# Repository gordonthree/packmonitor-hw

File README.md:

# Smart battery power monitor project

### A slim circuit board for managing charge and discharge of multi-cell LiFePo4 battery packs. Intended to track state of charge by coulomb counting and prevent battery pack damage from over discharge, over current and over temperature conditions.

## Goals:

1. Monitor and record total amperage in and out
2. Monitor and record temperature, ideally three places
3. Monitor and record pack voltage
4. Provide under-voltage disconnect
5. Provide over-temperature disconnect

## Features:

1. Atmel AVR Micro: ATMEGA4808 TQFP-32
1. Hall effect current sensor: TMCS1108 
   * Check my inventory for ACS7xx sensors!
1. FRAM data storage : I2C FM24C64B
1. Hot swap buffer: I2C TCA4311a, PCA9508
1. Host side i2c mux: PCA9545A
1. Max PCB width 18mm
1. Precision fixed resistor for thermistors
   * Thermistors: NRL1504F3950B1F
1.
   * MCU ADC does all measurements, for better or worse.

## Connectors:

1. Battery side
   * Battery In and Out (14 ga) - WAGO screw cage
   * 6-pin jst-xh vertical for three thermistors
1. Upstream interface: I2C
   * JST-xh 6-pin connector +5v, GND, SCL, GND, SDA, GND
   * TCA4311 on battery side
   * I2C switch on host side (might not need)

## Indicators:

* No onboard LEDs planned

## Client Commands:

* See [PackMonitor](https://github.com/gordonthree/packmonitor) for software details

## Questions:

* Will I finish in time?

## Resources:

#### ATMega4808:

* [https://www.digikey.com/en/products/detail/microchip-technology/ATMEGA4808-AUR/10444912](https://www.digikey.com/en/products/detail/microchip-technology/ATMEGA4808-AUR/10444912)
* [https://ww1.microchip.com/downloads/en/DeviceDoc/ATmega4808-09-DataSheet-DS40002173C.pdf](https://ww1.microchip.com/downloads/en/DeviceDoc/ATmega4808-09-DataSheet-DS40002173C.pdf)
* [https://github.com/MCUdude/MegaCoreX#pinout](https://github.com/MCUdude/MegaCoreX#pinout)

#### Thermistor:

* [https://www.digikey.com/en/products/detail/eaton-electronics-division/NRL1504F3950B1F/15927588](https://www.digikey.com/en/products/detail/eaton-electronics-division/NRL1504F3950B1F/15927588)
* [https://www.maximintegrated.com/en/design/technical-documents/app-notes/1/1753.html](https://www.maximintegrated.com/en/design/technical-documents/app-notes/1/1753.html)
* [https://www.jameco.com/Jameco/workshop/TechTip/temperature-measurement-ntc-thermistors.html](https://www.jameco.com/Jameco/workshop/TechTip/temperature-measurement-ntc-thermistors.html)

#### Readng precise voltages:

* [https://skillbank.co.uk/arduino/measure.htm](https://skillbank.co.uk/arduino/measure.htm)

#### ATMEGA Arduino:

* [https://github.com/MCUdude/MegaCoreX](https://github.com/MCUdude/MegaCoreX)

#### AVR DA / DB / DD Series:

* [https://github.com/SpenceKonde/DxCore](https://github.com/SpenceKonde/DxCore)
#### Bootloader:

* [https://github.com/Optiboot/optiboot](https://github.com/Optiboot/optiboot)

#### FRAM:

* [FM24C64B](https://www.digikey.com/en/products/detail/cypress-semiconductor-corp/FM24C64B-GTR/3788931)

#### Hall Effect Sensor:

* [https://www.ti.com/product/TMCS1108](https://www.ti.com/product/TMCS1108)

#### Hot swap buffers:

* [https://www.digikey.com/en/products/detail/nxp-usa-inc/PCA9545AD-118/789953](https://www.digikey.com/en/products/detail/nxp-usa-inc/PCA9545AD-118/789953)

* [https://www.ti.com/product/TCA4311A?qgpn=tca4311a](https://www.ti.com/product/TCA4311A?qgpn=tca4311a)
#### Switching regulator (tiny):

* [https://www.diodes.com/assets/Datasheets/AP62200_AP62201_AP62200T.pdf](https://www.diodes.com/assets/Datasheets/AP62200_AP62201_AP62200T.pdf)

#### ADC:

* [https://www.nuvoton.com/export/resource-files/NAU7802%20Data%20Sheet%20V1.7.pdf](https://www.nuvoton.com/export/resource-files/NAU7802%20Data%20Sheet%20V1.7.pdf)

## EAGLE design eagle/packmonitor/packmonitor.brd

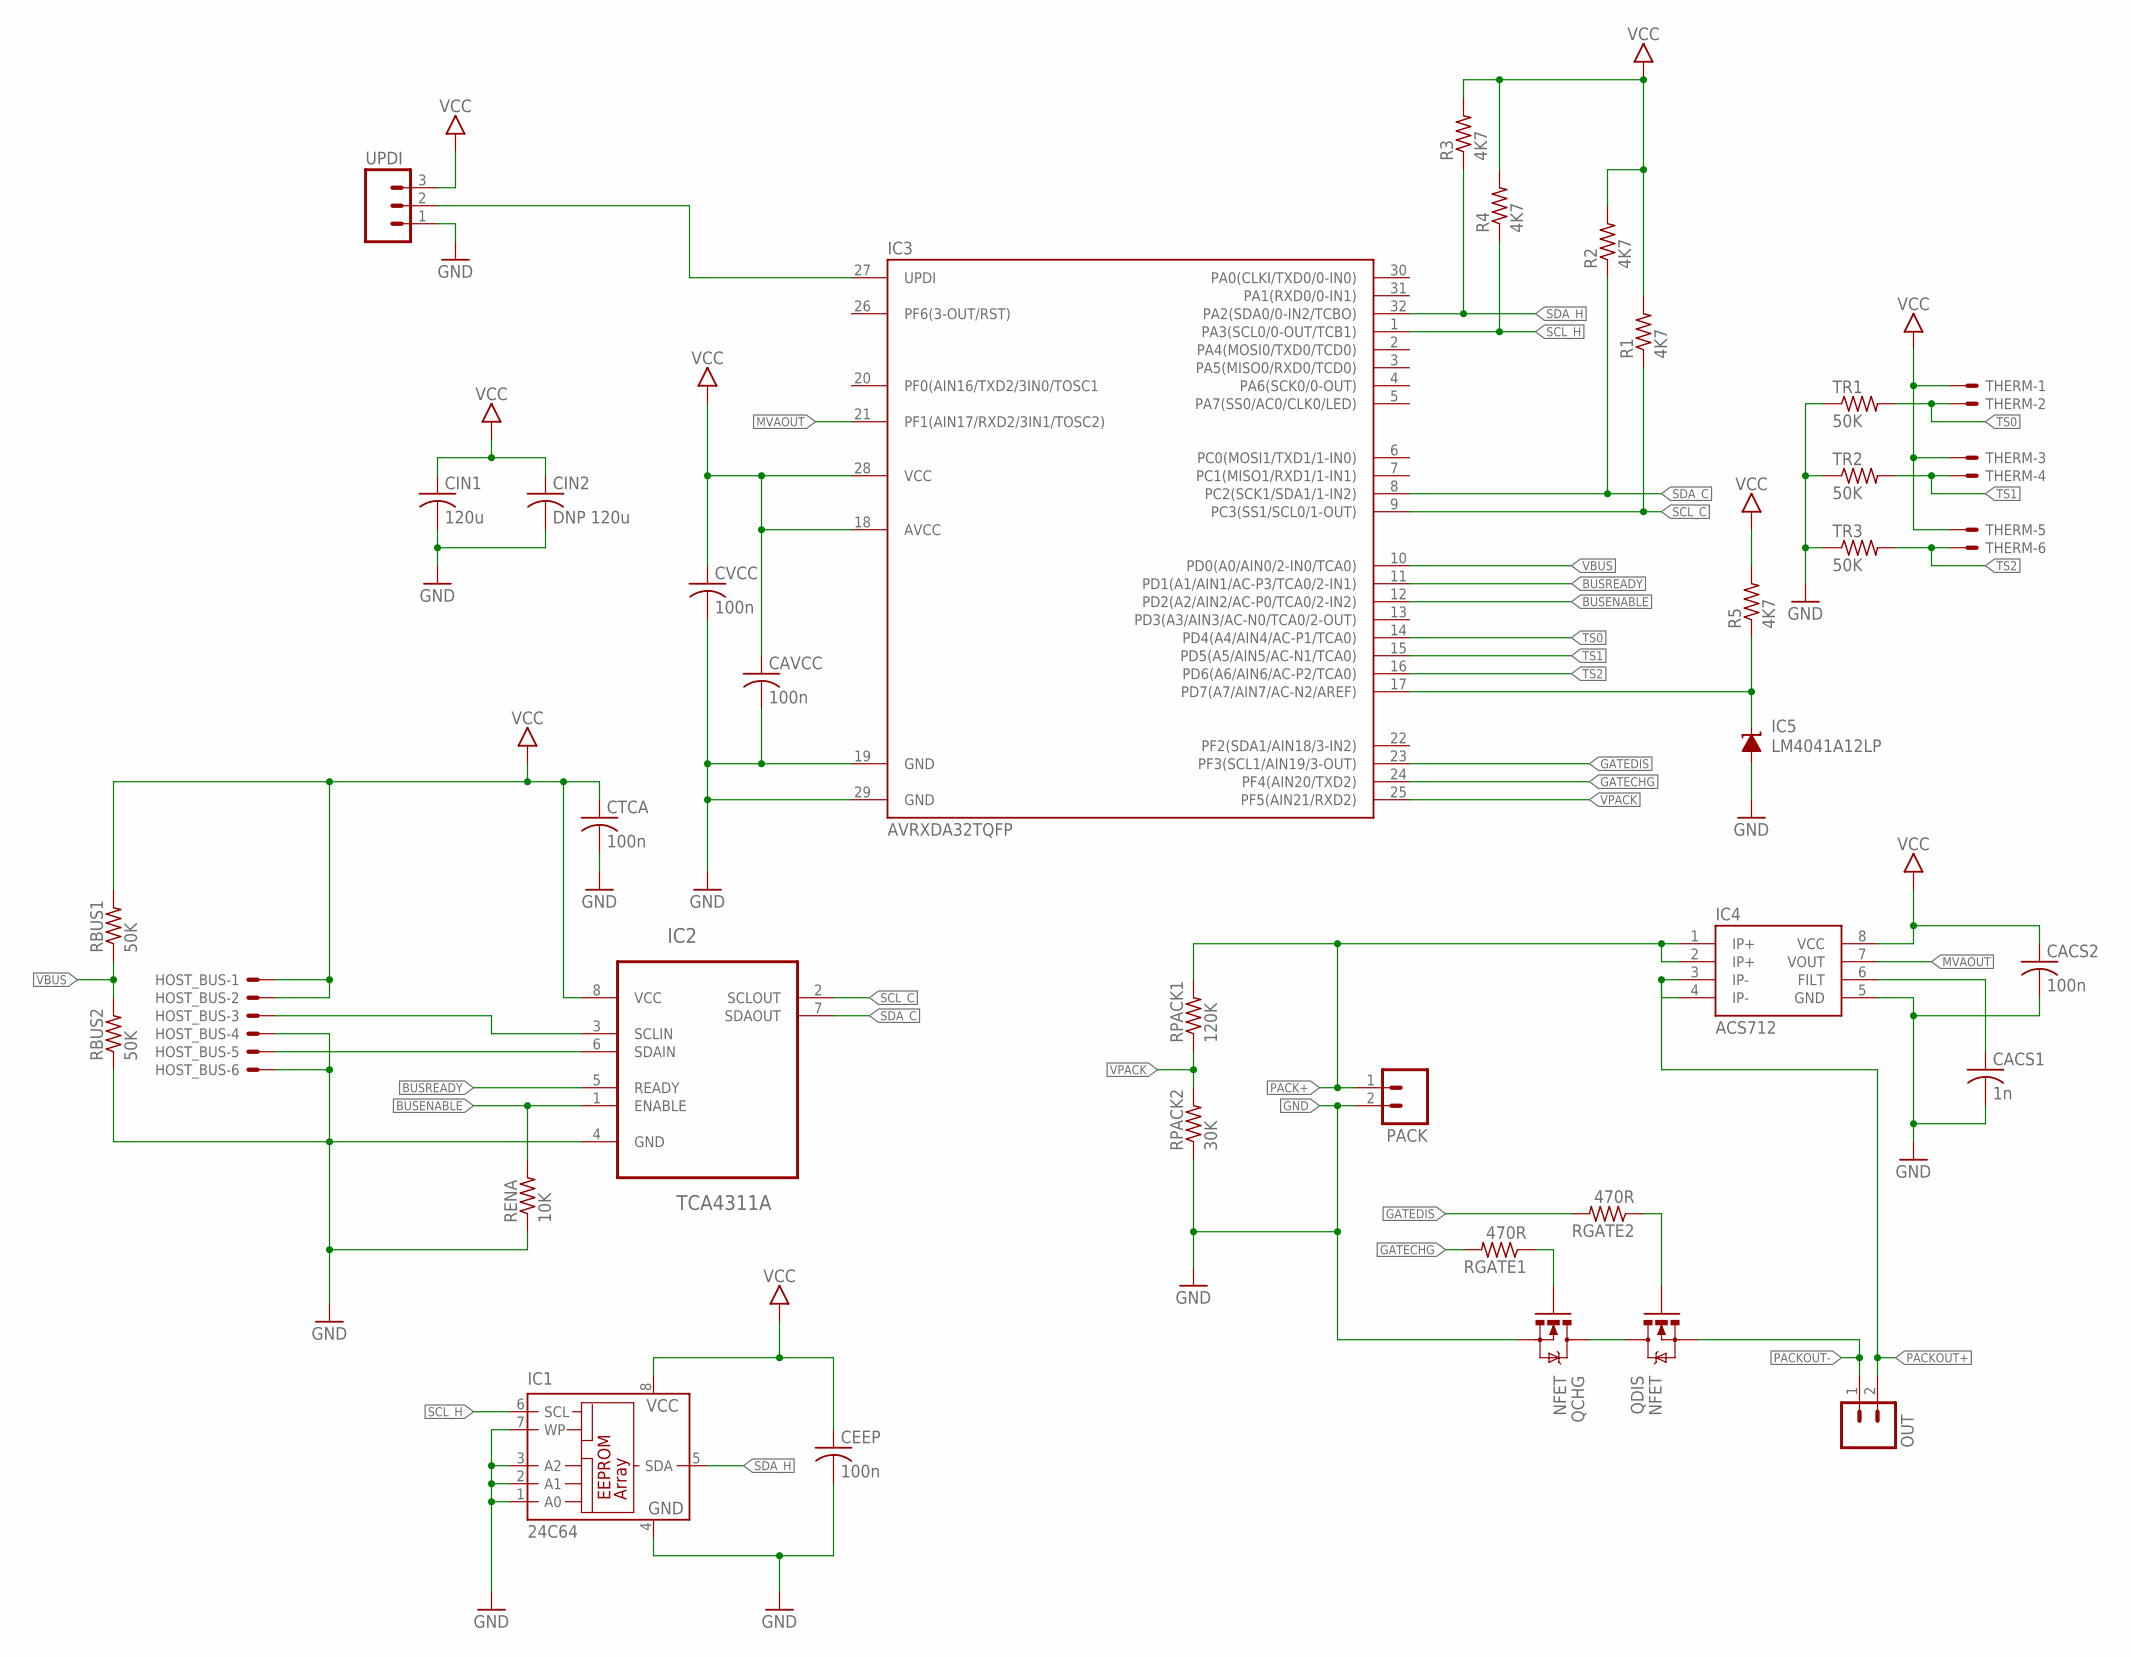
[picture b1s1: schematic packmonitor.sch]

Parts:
CACS1: 1n; C0603
CACS2: 100n; C0603
CAVCC: 100n; C0603
CEEP: 100n; C0603
CIN1: 120u; C1206
CIN2: DNP 120u; C1206
CTCA: 100n; C0603
CVCC: 100n; C0603
HOST_BUS: JST-XH-06-PIN-LONG-PAD; JST-XH-06-PACKAGE-LONG-PAD
IC1: 24C64; SO-08
IC2: TCA4311A; SOIC127P600X175-8N
IC3: AVRXDA32TQFP; TQFP32-08
IC4: ACS712; SO08
IC5: LM4041A12LP; LP_O-PBCY-W3
OUT: M023.5MM; SCREWTERMINAL-3.5MM-2
PACK: M023.5MM; SCREWTERMINAL-3.5MM-2
QCHG: NFET; SO08
QDIS: NFET; SO08
R1, R2, R3, R4, R5: 4K7; R0603
RBUS1, RBUS2: 50K; R0805
RENA: 10K; R0603
RGATE1, RGATE2: 470R; R0603
RPACK1: 120K; R0805
RPACK2: 30K; R0805
THERM: JST-XH-06-PIN-ROUND-PAD; JST-XH-06-PACKAGE-ROUND-PAD
TR1, TR2, TR3: 50K; R0805
UPDI: M03PTH; 1X03

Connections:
BUSENABLE: IC2.1 (ENABLE), IC3.12 (PD2(A2/AIN2/AC-P0/TCA0/2-IN2)), RENA.2
BUSREADY: IC2.5 (READY), IC3.11 (PD1(A1/AIN1/AC-P3/TCA0/2-IN1))
GATECHG: IC3.24 (PF4(AIN20/TXD2)), RGATE1.2
GATEDIS: IC3.23 (PF3(SCL1/AIN19/3-OUT)), RGATE2.2
GND: CACS1.2, CACS2.2, CAVCC.2, CEEP.2, CIN1.2, CIN2.2, CTCA.2, CVCC.2, HOST_BUS.4, HOST_BUS.6, IC1.1 (A0), IC1.2 (A1), IC1.3 (A2), IC1.4 (GND), IC1.7 (WP), IC2.4 (GND), IC3.19 (GND), IC3.29 (GND), IC4.5 (GND), IC5.3 (A), PACK.2, QCHG.1 (S), QCHG.2 (S), QCHG.3 (S), RBUS2.1, RENA.1, RPACK2.1, TR1.1, TR2.1, TR3.1, UPDI.1
MVAOUT: IC3.21 (PF1(AIN17/RXD2/3IN1/TOSC2)), IC4.7 (VOUT)
unnamed: QCHG.4 (G), RGATE1.1
unnamed: QDIS.4 (G), RGATE2.1
unnamed: CACS1.1, IC4.6 (FILT)
unnamed: IC3.17 (PD7(A7/AIN7/AC-N2/AREF)), IC5.2 (C), R5.1
PACK+: IC4.1 (IP+), IC4.2 (IP+), PACK.1, RPACK1.2
PACKOUT+: IC4.3 (IP-), IC4.4 (IP-), OUT.2
PACKOUT-: OUT.1, QDIS.1 (S), QDIS.2 (S), QDIS.3 (S)
PDISC: QCHG.5 (D), QCHG.6 (D), QCHG.7 (D), QCHG.8 (D), QDIS.5 (D), QDIS.6 (D), QDIS.7 (D), QDIS.8 (D)
SCLIN: HOST_BUS.3, IC2.3 (SCLIN)
SCL_C: IC2.2 (SCLOUT), IC3.9 (PC3(SS1/SCL0/1-OUT)), R1.1
SCL_H: IC1.6 (SCL), IC3.1 (PA3(SCL0/0-OUT/TCB1)), R4.1
SDAIN: HOST_BUS.5, IC2.6 (SDAIN)
SDA_C: IC2.7 (SDAOUT), IC3.8 (PC2(SCK1/SDA1/1-IN2)), R2.1
SDA_H: IC1.5 (SDA), IC3.32 (PA2(SDA0/0-IN2/TCBO)), R3.1
TS0: IC3.14 (PD4(A4/AIN4/AC-P1/TCA0)), THERM.2, TR1.2
TS1: IC3.15 (PD5(A5/AIN5/AC-N1/TCA0)), THERM.4, TR2.2
TS2: IC3.16 (PD6(A6/AIN6/AC-P2/TCA0)), THERM.6, TR3.2
UPDI: IC3.27 (UPDI), UPDI.2
VBUS: IC3.10 (PD0(A0/AIN0/2-IN0/TCA0)), RBUS1.1, RBUS2.2
VCC: CACS2.1, CAVCC.1, CEEP.1, CIN1.1, CIN2.1, CTCA.1, CVCC.1, HOST_BUS.1, HOST_BUS.2, IC1.8 (VCC), IC2.8 (VCC), IC3.18 (AVCC), IC3.28 (VCC), IC4.8 (VCC), R1.2, R2.2, R3.2, R4.2, R5.2, RBUS1.2, THERM.1, THERM.3, THERM.5, UPDI.3
VPACK: IC3.25 (PF5(AIN21/RXD2)), RPACK1.1, RPACK2.2

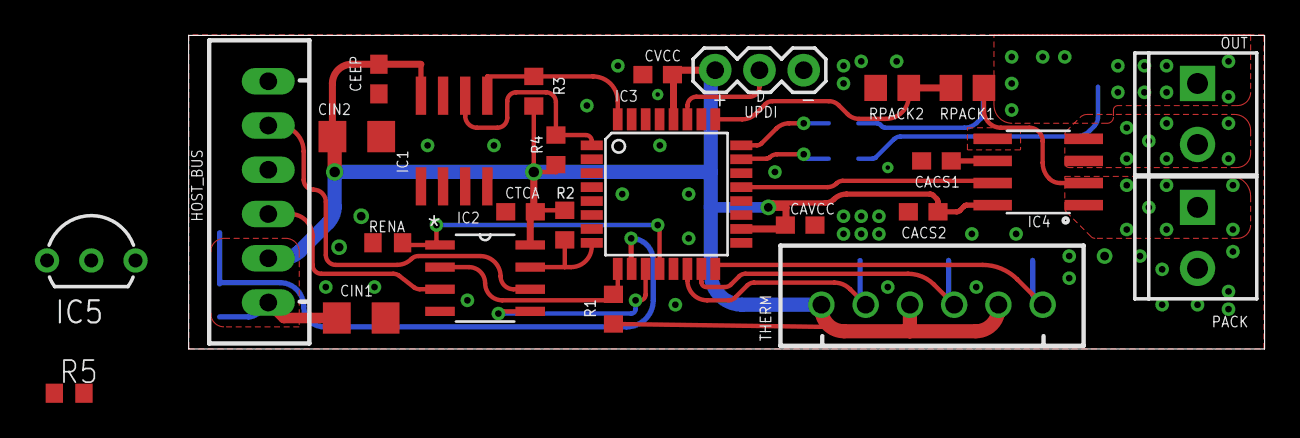
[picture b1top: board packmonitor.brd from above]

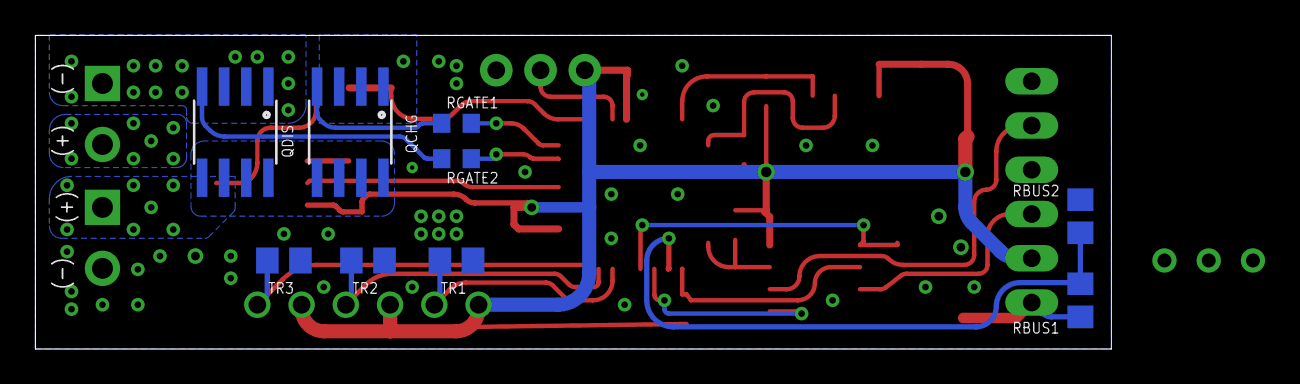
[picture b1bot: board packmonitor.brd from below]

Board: 2 copper layers, 61.8 x 18.0 mm, 35 parts (9 on the bottom side), 27 nets.

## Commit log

2022-08-02 Moved PackMonitor hardware to separate repo
2022-08-02 created new repo for packmonitor hardware
2022-08-02 got rid of input power switch
2022-08-02 updated readme to reflect "simplified" design
2022-08-02 Updated packmonitor repo url
2022-08-02 more tweaks
2022-08-02 fixing formatting hopefully
2022-08-17 added da chips
2022-08-17 switched to avr128da32 chip & low side disconnect
2022-08-17 layout and routing complete, needs fine tuning
2022-08-17 final tweaks, fingers crossed order sent
2022-08-19 Added pull up resistors on i2c busses
2022-08-19 Cleanup labels for new resistors
2022-08-19 Added prevision 2.5v reference, need to get the shoehorn.

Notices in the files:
parts and their libraries:
SparkFun-Connectors: Licensing: Creative Commons ShareAlike 4.0 International - https://creativecommons.org/licenses/by-sa/4.0
